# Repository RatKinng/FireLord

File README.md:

# FireLord Sensor Network Platform

FireLord is an open hardware reference for low-cost, peer-to-peer sensor meshes. The repository captures mechanical models, firmware helpers, PCB files, and planning artifacts produced during an Alaskan field concept so future teams can reuse or adapt the design.

---

## Intended Audience

- Municipal and resource agencies that need rapidly deployable sensor coverage.
- Community groups and educators building inexpensive environmental monitors.
- Integrators evaluating FireLord as a foundation for broader sensing programs.

---

## Repository Map

| Path | Contents |
| --- | --- |
| [`device-firmware/`](device-firmware/README.md) | Arduino-oriented helpers for sensor sampling and LoRa communication. |
| [`device-case/`](device-case/README.md) | 3D models, print notes, and assembly guidance for the field enclosure. |
| [`pcb-and-schematics/`](pcb-and-schematics/README.md) | KiCad project for the carrier board and custom footprints. |
| [`database-firelord/`](database-firelord/README.md) | Preferred: host-run USB logger that writes base-station packets into Postgres with a simple web viewer. |

---

## System Overview

1. **Field nodes** collect local sensor data, flag anomalies, and rebroadcast peer packets.  
2. **Base stations** are FireLord nodes flashed in base-station mode (no sensors, receive-only) that log every packet over USB serial and forward data when backhaul is available.  
3. **Optional cloud services** expose data to stakeholders or downstream tooling.

The mesh design keeps infrastructure light: any node can relay data, and a single active base station is sufficient.

---

## Quick Start

1. Review the operating targets below (range, duty cycle, enclosure limits) and adjust for your field conditions.  
2. Select components from the baseline bill of materials; plan on roughly $75 per node at 100-unit scale.  
3. Manufacture or print hardware following the subsystem READMEs.  
4. Load the firmware scaffold, confirm sensor and LoRa links, and tailor packet contents.  
5. Deploy nodes so each device reaches two peers or a base station, then validate end-to-end logging.

Use the risk guidance below while planning; the most common issues are supply delays, isolated nodes, and inadequate solar input.

---

## Operating Targets

- Peer-to-peer LoRa range: design for non-line-of-sight coverage of at least 500 m between nodes; verify in your terrain.  
- Reporting cadence: transmit sensor packets no less frequently than every 60 s unless power constraints dictate a longer interval.  
- Receive availability: keep the radio in a ready state to forward peer traffic continuously.  
- Data bandwidth: maintain ≥ 1.2 KB/s (9600 baud) for device-to-device links.  
- Power: average receive-ready draw ≤ 100 mW with duty-cycled heaters; energy storage provided by supercapacitors only.  
- Mechanical envelope: keep external dimensions within 200 mm per axis to fit the reference enclosure.  
- Environmental durability: target IP55 ingress protection and verified operation down to −30 °C for at least 30 min.  
- Radio spectrum: operate in the regional sub-GHz LoRa band (e.g., 902–928 MHz in North America) with a fixed-length header and byte-structured frame format.  
- Bill of materials: $75 per node is achievable at 100-unit quantities using the parts listed below.

---

## Deployment Notes

- **Topology**: Maintain overlapping coverage; document approved node spacing before field work.  
- **Placement**: Mount above snow or vegetation, shield cables from wildlife, and orient vents downward.  
- **Backhaul**: Configure the base station to cache indefinitely; cloud transfer is optional.  
- **Operations**: Schedule inspections ahead of seasonal activities (e.g., controlled burns or tourism peaks).

---

## Ground Operations (Base-Station Logging)

- Use `database-firelord/` for the lightweight flow: start Postgres via Docker (`start.sh` or `start.ps1`), run the host logger to read the base-station USB serial (set `SERIAL_PORT` to your COM/tty), and view recent packets in the bundled web viewer. See `database-firelord/README.md` for setup, dedup behavior, and testing without hardware.
- The historical COSMOS stack used earlier is no longer part of this repo; the database-firelord logger is the supported path going forward.

---

## Hardware Snapshot

| Component | Key details | Mount style | Unit cost (USD, 2-unit qty) | Remarks |
| --- | --- | --- | --- | --- |
| [LoRa module (Reyax RYLR998)](https://www.digikey.com/en/products/detail/reyax/RYLR998/22078252) | 3.3 V P2P radio | Through-hole module | 16.90 | Ships on a carrier with 2.54 mm headers; can be socketed or wired directly without reflow. |
| [MCU (Seeeduino XIAO SAMD21)](https://www.digikey.com/en/products/detail/seeed-technology-co-ltd/102010328/11506471) | Arduino-compatible controller | Castellated SMD | 5.40 | Hand-solderable to the XIAO footprint; DIP adapters are available if you prefer header pins. |
| [CO₂/temp/humidity sensor (Sensirion SCD40)](https://www.digikey.com/en/products/detail/sensirion-ag/SCD40-D-R2/13684008) | I²C environmental sensing | LGA SMD | 17.95 | Use a breakout like the [SparkFun SEN-18360](https://www.sparkfun.com/products/18360) when avoiding reflow. |
| [CO sensor (MQ-7)](https://www.digikey.com/en/products/detail/olimex-ltd/SNS-MQ7/21662604) | Analog gas sensor | Through-hole | 5.65 | Duty-cycle the heater to save power. |
| [Pressure sensor (NXP MPL115A2)](https://www.digikey.com/en/products/detail/nxp-usa-inc/MPL115A2ST1/16538791) | I²C barometer | LGA SMD | 4.75 | Choose a breakout (Adafruit 992 or similar) if assembling without reflow. |
| [Smoke sensor (DFRobot SEN0570)](https://www.digikey.com/en/products/detail/dfrobot/SEN0570/24611153) | Analog particle indicator | Module w/2.54 mm header | 4.90 | Mount behind vent mesh. |
| [VOC sensor (DFRobot SEN0566)](https://www.digikey.com/en/products/detail/dfrobot/SEN0566/24611145) | Analog VOC indicator | Module w/2.54 mm header | 4.90 | Co-locate with smoke sensor. |
| [Supercapacitor (Tecate TPLH-2R7-800)](https://www.digikey.com/en/products/detail/tecate-group/TPLH-2R7-800PS35X71/21378858) | 2.7 V 800 F storage | Radial through-hole | 17.50 (each) | Use two in series with balancing. |
| [Base-station node (FireLord in BASE_STATION_MODE)](https://www.digikey.com/en/products/detail/seeed-technology-co-ltd/102010328/11506471) | USB-powered receive-only gateway | Onboard | 5.40 + radio | Same hardware as field nodes; flash with `BASE_STATION_MODE=true` and omit sensors. |
| [Solar panel (Seeed 1 W)](https://www.mouser.com/ProductDetail/Seeed-Studio/313070001) | 5 V nominal, 1 W | Leaded | 11.95 | Size array for local insolation. |
| [Connectors, cabling, misc.](https://www.amazon.com/100Pcs-Connector-Include-Female-Ph2-0mm/dp/B0DMW21LWS) | JST harnesses, fasteners | Through-hole / pre-crimped | ~10.00 | Include spare gaskets and glands. |

Estimated total: ≈ $75 per field node at 100-unit scale. Choosing breakout boards for the SMD-only sensors raises cost slightly but simplifies assembly when reflow is unavailable.

---

## Power Profile

- 283 mW: receive-ready state with high-draw sensors active.  
- 116 mW: duty-cycled average with smoke/VOC heaters at 5 % duty.  
- 600 mAh equivalent storage supports ~7 h at peak load and ~17 h at averaged load.

Adjust sampling cadence, heater duty cycles, or panel capacity to meet local endurance goals.

---

## Risk Summary

| Theme | Mitigation |
| --- | --- |
| Part delays | Order early, maintain alternates, record substitutions. |
| Node isolation | Pre-survey install sites, document minimum spacing, train field crews. |
| Power loss | Site panels in clear sun, inspect seasonally, log low-voltage events. |
| Sensor drift | Implement firmware sanity checks; schedule recalibration windows. |
| Base station downtime | Provide backup power and confirm local logging before field work. |

Document mitigations and revisit them seasonally to keep deployments stable.

---

## Extending the Platform

- Add routing intelligence, adaptive transmit power, or health beacons for larger meshes.  
- Integrate SMS, dashboard, or API publishing pipelines.  
- Incorporate soil probes, weather stations, or perimeter sensors.  
- Package sensor pods for quick swap service.  
- Expand packet signing or integrity checks for regulated deployments.

---

## Prototype Artifacts

- Work breakdowns and PERT charts outline the original build sequence.  
- Firmware helpers (`I2C_COMMS`, `UART_COMMS`) provide safe defaults for sensor and radio access.  
- Mechanical CAD documents enclosure iterations and tolerance tests.

Use these as reference when creating production-ready variants.

---

## System Characteristics

- **Operating profile**: LoRa P2P mesh at 915 MHz (example: SF7, 125 kHz BW, CR 4/5, 10 dBm) with receive-ready nodes and 60 s sampling. Packets are fixed-length (23 bytes payload + CRC32) with flag bits for outliers and a rolling CRC buffer to block duplicates.  
- **Performance targets**: ≥ 500 m NLOS hops, ≥ 1.2 KB/s link budget (9600 baud), IP55 enclosure, −30 °C for 30 min, and < 200 mm mechanical span. Power: 283 mW RX-ready with heaters on; ≈116 mW average at 5 % heater duty. 600 mAh-equivalent storage yields ~7 h peak or ~17 h average runtime. BOM ≈ $75 per node at 100-unit quantities.  
- **Radio and payload**: Example initialization uses `AT`, `AT+MODE=TEST`, `AT+TEST=RFCFG,…`, `AT+TEST=RXLRPKT`; `UART_COMMS::p2pTxHex` waits for `+TEST: TX DONE`. Payload layout mirrors `device-firmware/FireLordNode` suggestions (version, device ID, timestamp, temperature, humidity, CO₂, CO, pressure, smoke, VOC, flags, CRC32).  
- **Electronics**: KiCad carrier hosts a Seeeduino XIAO (I²C, UART, analog), Reyax/Wio-E5 radio, and connectors for SCD40, MPL115A2, MQ-7, smoke, and VOC sensors. Supercapacitor pads include balancing; test pads expose 3.3 V, ground, UART TX/RX, and reset. Footprints favor hand assembly; run ERC/DRC, then generate Gerbers and pick-and-place before fab.  
- **Firmware behavior**: Samples I²C sensors via `I2C_COMMS`, analog after heater warm-up, validates ranges, packages the frame, records CRC history, and transmits through `UART_COMMS`. Bench mode seeds data when sensors are absent. Power practices include MOSFET-controlled heaters, RTC/low-power sleep, and voltage checks to gate TX.  
- **Enclosure and assembly**: `device-case` contains Fusion 360, STEP, 3MF, and OpenSCAD sources. Print with PETG/ASA/PC, 0.2 mm layers, ≥ 3 perimeters, 20 % infill; gaskets in TPU or 2 mm silicone. Assembly sequence: seat gasket, mount PCB on M3 standoffs, route solar/antenna through glands with strain relief, close lid diagonally, add vent mesh. Use conformal coating and desiccant; vents should face down. Heat/flame resistance is not provided.  
- **Deployment and validation**: Maintain overlapping node coverage, mount above vegetation/snow, shield cables, and cache packets indefinitely at the base-station node on USB serial. Validation steps: pre/post I²C scans, `LoRaE5::ping()`, inspect TX/RX/FWD serial logs (including `DATA …`) for delivery, and record hop counts during field trials. Revisit risk mitigations seasonally (supply, isolation, power, sensor drift, base-station uptime).  
- **Extension paths**: OTA or signed updates, adaptive routing/TX power, cloud/API publishing, additional sensors (soil, weather, perimeter), antenna/housing variants, and SMA with controlled impedance for external antennas.

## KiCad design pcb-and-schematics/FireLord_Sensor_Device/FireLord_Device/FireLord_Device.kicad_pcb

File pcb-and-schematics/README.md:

# Electronics Design Guide

The KiCad project in this directory defines the sensor carrier board used by FireLord. It is suitable for small fabrication runs and straightforward to adapt for alternate sensors or power stages.

---

## Project Layout

```
Pressure_Sensor/
└── Pressure_Sensor_Board/
    ├── Pressure_Sensor_Board.kicad_pro
    ├── Pressure_Sensor_Board.kicad_sch
    ├── Pressure_Sensor_Board.kicad_pcb
    ├── PressureSensor.pretty/
    └── fp-lib-table
```

Open the `.kicad_pro` file in KiCad 7+. If footprints appear missing, point KiCad to the bundled `PressureSensor.pretty` library.

---

## Circuit Highlights

- Seeeduino XIAO header exposing I²C, UART, analog, and power rails.  
- JST or locking connectors for CO, smoke, VOC, and other sensor daughterboards.  
- SCD40 and MPL115A2 wired on a shared I²C bus with 400 kHz pull-ups.  
- Supercapacitor pads with balancing resistors and space for optional regulators.  
- Test pads for 3.3 V, ground, UART TX/RX, and reset.

Trace widths and component spacing were selected for easy hand assembly.

---

## Fabrication Workflow

1. Run ERC/DRC and resolve any violations.  
2. Generate Gerbers, drills, and pick-and-place files; archive each release (e.g., `fab/2025-03-RevA/`).  
3. Order 1.6 mm FR-4, 1 oz copper boards from your preferred supplier.  
4. Assemble SMD parts first, then supercapacitors and connectors.  
5. Verify I²C devices with the firmware scan and confirm LoRa UART signalling before enclosure install.

---

## Customization Notes

- Update footprints and BOM items when swapping sensors; confirm mechanical clearance against the enclosure model.  
- Replace the supercapacitor block with LiFePO₄ hardware if longer runtime is required.  
- Add extra headers for status LEDs, buttons, or expansion harnesses.  
- Introduce an SMA footprint with controlled impedance if you need external antennas.

Record every change with a new schematic and PCB revision.

---

## Footprint Library

`PressureSensor.pretty` contains enlarged pads for hand soldering. If you fork the design, duplicate the library and keep naming conventions (e.g., `FLD_SENSOR_*`) so scripts resolve correctly. Export 3D models as needed for enclosure fit checks.

---

## Additional Notes

- BOM reference: LoRa radio $16.90, Seeeduino $5.40, SCD40 $17.95, supercapacitors $17.50 each, remaining sensors $5–$10.  
- Environmental targets: IP55 enclosure, −30 °C survivability for 30 min, and a 200 mm maximum dimension to fit the printed housing.  
- Common risks: delayed component deliveries, insufficient node density, and inadequate solar exposure; plan mitigations during layout and procurement.

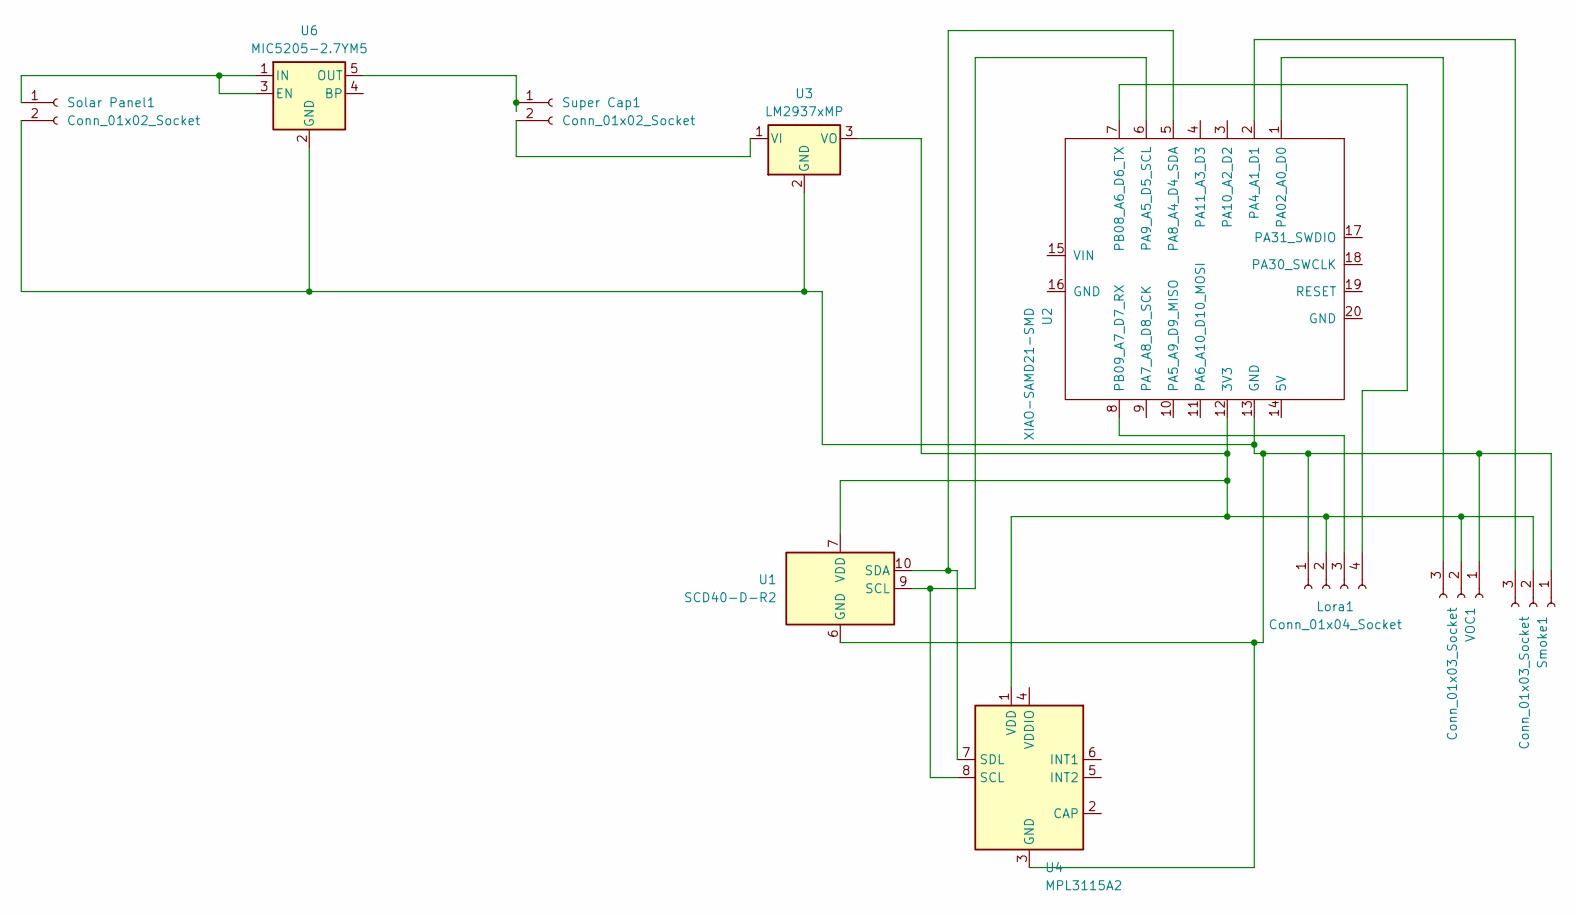
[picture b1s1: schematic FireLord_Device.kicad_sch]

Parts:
Lora1: Conn_01x04_Socket; JST_EH_B4B-EH-A_1x04_P2.50mm_Vertical
Smoke1: Conn_01x03_Socket; FanPinHeader_1x03_P2.54mm_Vertical
Solar Panel1: Conn_01x02_Socket; JST_XA_B02B-XASK-1-A_1x02_P2.50mm_Vertical
Super Cap1: Conn_01x02_Socket; JST_XA_B02B-XASK-1-A_1x02_P2.50mm_Vertical
U1: SCD40-D-R2; Sensirion_SCD4x-1EP_10.1x10.1mm_P1.25mm_EP4.8x4.8mm
U2: XIAO-SAMD21-SMD
U3: LM2937xMP; SOT-223-3_TabPin2
U4: MPL3115A2; NXP_LGA-8_3x5mm_P1.25mm_H1.1mm
U6: MIC5205-2.7YM5; SOT-23-5
VOC1: Conn_01x03_Socket; FanPinHeader_1x03_P2.54mm_Vertical

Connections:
unnamed: Lora1.1, Smoke1.1, Solar Panel1.2, U1.6 (GND), U1.20 (GND), U1.21 (GND), U2.13 (GND), U3.2 (GND), U4.3 (GND), U6.2 (GND), VOC1.1
unnamed: Lora1.2, Smoke1.2, U1.7 (VDD), U1.19 (VDD), U2.12 (3V3), U3.3 (VO), U4.1 (VDD), VOC1.2
unnamed: Lora1.3, U2.8 (PB09_A7_D7_RX)
unnamed: Lora1.4, U2.7 (PB08_A6_D6_TX)
unnamed: Smoke1.3, U2.2 (PA4_A1_D1)
unnamed: Solar Panel1.1, U6.1 (IN), U6.3 (EN)
unnamed: Super Cap1.1, U6.5 (OUT)
unnamed: Super Cap1.2, U3.1 (VI)
unnamed: U1.9 (SCL), U2.6 (PA9_A5_D5_SCL), U4.8 (SCL)
unnamed: U1.10 (SDA), U2.5 (PA8_A4_D4_SDA), U4.7 (SDL)
unnamed: U2.1 (PA02_A0_D0), VOC1.3

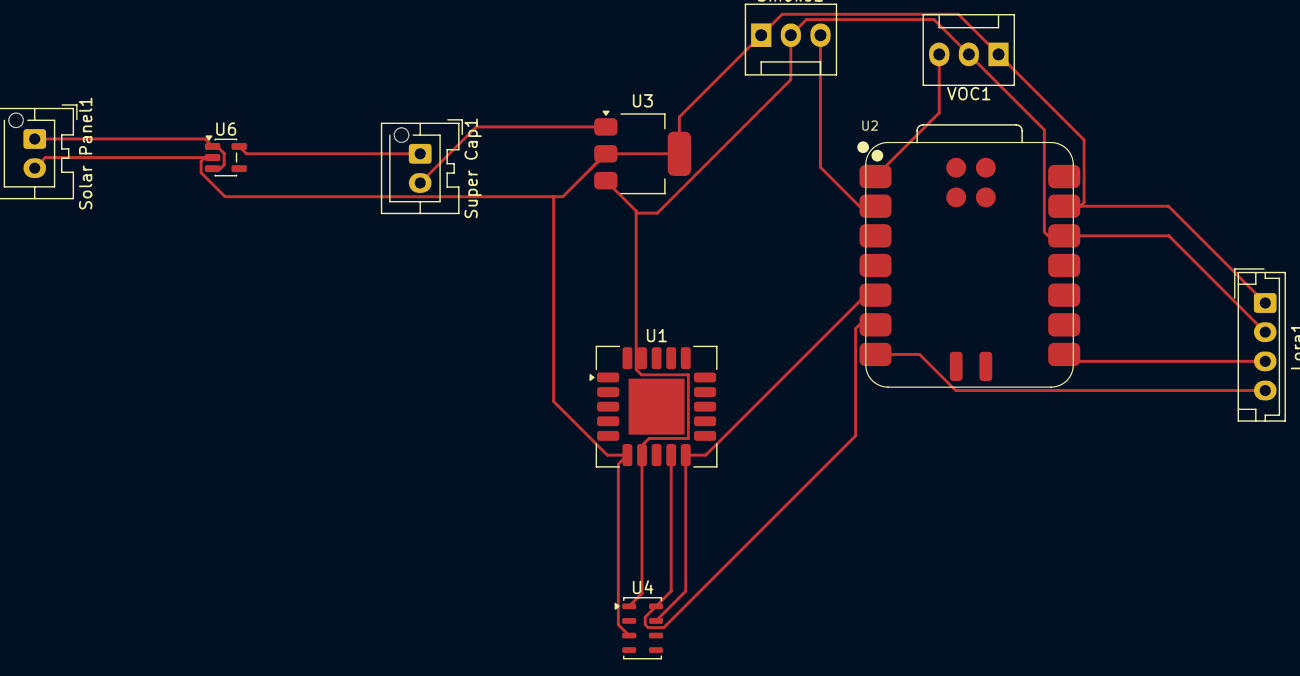
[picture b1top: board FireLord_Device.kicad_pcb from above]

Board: 2 copper layers, 10 parts (0 on the bottom side), 11 nets.

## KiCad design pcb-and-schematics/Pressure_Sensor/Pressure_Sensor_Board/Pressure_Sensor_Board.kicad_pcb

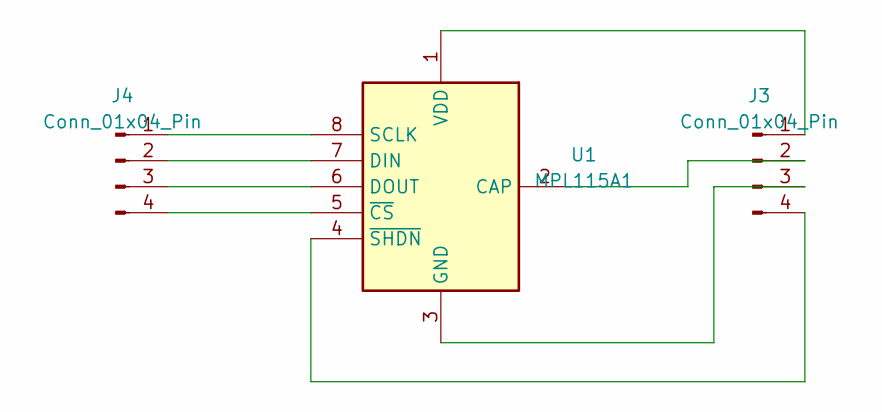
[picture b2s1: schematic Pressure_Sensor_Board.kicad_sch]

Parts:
J3, J4: Conn_01x04_Pin; PinHeader_1x04_P1.27mm_Vertical
U1: MPL115A1; NXP_LGA-8_3x5mm_P1.25mm_H1.2mm

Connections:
unnamed: J3.1, U1.1 (VDD)
unnamed: J3.2, U1.2 (CAP)
unnamed: J3.3, U1.3 (GND)
unnamed: J3.4, U1.4 (~SHDN)
unnamed: J4.1, U1.8 (SCLK)
unnamed: J4.2, U1.7 (DIN)
unnamed: J4.3, U1.6 (DOUT)
unnamed: J4.4, U1.5 (~CS)

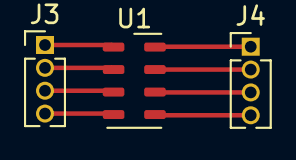
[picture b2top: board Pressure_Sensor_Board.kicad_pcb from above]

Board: 2 copper layers, 3 parts (0 on the bottom side), 8 nets.

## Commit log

2025-10-08 Added Pressure sensor adaptor board files under PCB_And_Schematics/Pressure_Sensor
2025-10-09 Fixed spelling.
2025-10-09 COSMOS working, trying to push to github.
2025-10-10 COSMOS
2025-11-05 Final working LoRa code, updated case files, documentation.
2025-11-12 Moved things out of erronious directory.
2025-11-17 Device PCB
2025-12-01 Arduino file must be withint subdirectory.
2025-12-01 Removed erronious files.
2025-12-01 Added useful into to README.
2025-12-01 does this work?
2025-12-01 try this
2025-12-01 maybe this?
2025-12-01 Add Laravel files directly to the repository
2025-12-01 Add openc3 files directly to the repository
2025-12-01 trying
2025-12-01 add openc3 files
2025-12-01 try again
2025-12-01 trying this
2025-12-01 trying again?
2025-12-01 removed submodule
2025-12-01 USB submodule removed
2025-12-03 Updated READMEs for COSMOS.
2025-12-03 Added base station mode, bypassing the LoRa USB module entirely.
2025-12-03 Sensor logic is now disabled in base station mode (assumes no sensors are connected).
2025-12-03 Removed all mentions of the wretched proprietary USB LoRa E22 dongle.
2025-12-03 Initial commit of simpler database system, removing cosmos entirely (overkill, overcomplicated).
2025-12-04 Split USB logger from container; run Postgres only and add host tools - replace SQLite/containerized logger with host-run Python that streams DATA lines into Postgres over TCP, plus setup/ start scri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
2025-12-04 Fixed to support 5 second rate of temp/humidity/co2 sensor.
2025-12-04 Fixed web interface misinterpretations and missing data.
